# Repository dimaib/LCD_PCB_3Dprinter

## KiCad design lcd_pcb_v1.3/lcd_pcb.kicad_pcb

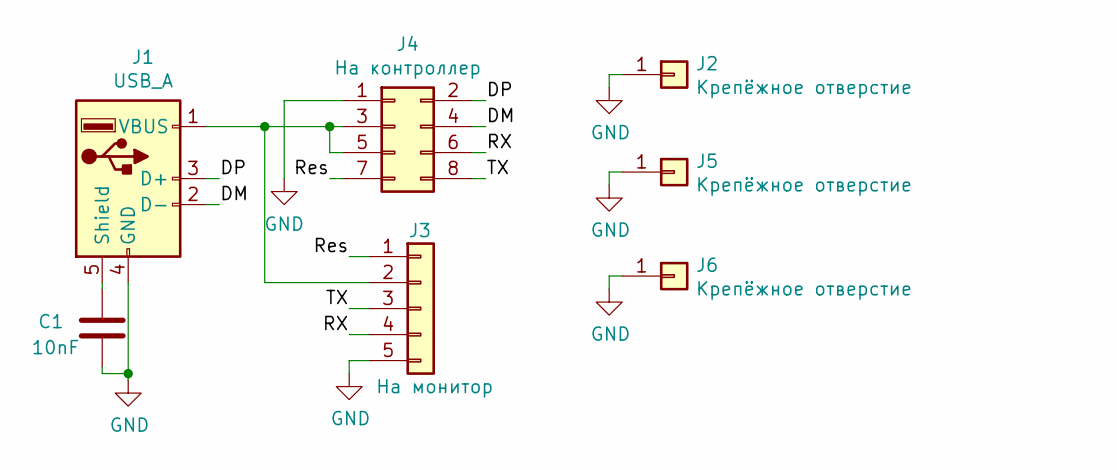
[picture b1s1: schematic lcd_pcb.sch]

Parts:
C1: 10nF; C_0603_1608Metric
J1: USB_A; USB_A_CONNFLY_DS1095-WNR0
J2, J5, J6: Крепёжное отверстие; MountingHole_2.2mm_M2_Pad_Via
J3: На монитор; lcd
J4: На контроллер; IDC-Header_2x04_P2.54mm_Vertical

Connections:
/DM: J1.2 (D-), J4.4
/DP: J1.3 (D+), J4.2
/RX: J3.4, J4.6
/Res: J3.1, J4.7
/TX: J3.3, J4.8
GND: C1.2, J1.4 (GND), J2.1, J3.5, J4.1, J5.1, J6.1
unnamed: C1.1, J1.5 (Shield)
unnamed: J1.1 (VBUS), J3.2, J4.3, J4.5

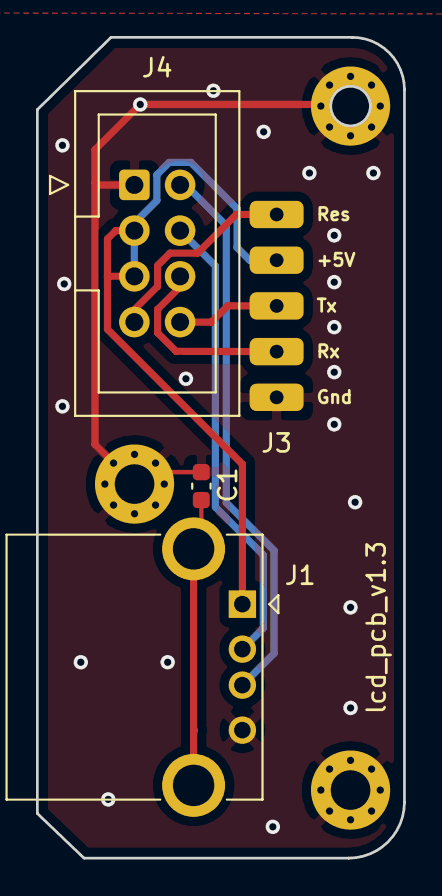
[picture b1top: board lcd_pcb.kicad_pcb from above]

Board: 2 copper layers, 20.4 x 45.6 mm, 7 parts (0 on the bottom side), 8 nets.

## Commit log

2022-04-24 add screen
